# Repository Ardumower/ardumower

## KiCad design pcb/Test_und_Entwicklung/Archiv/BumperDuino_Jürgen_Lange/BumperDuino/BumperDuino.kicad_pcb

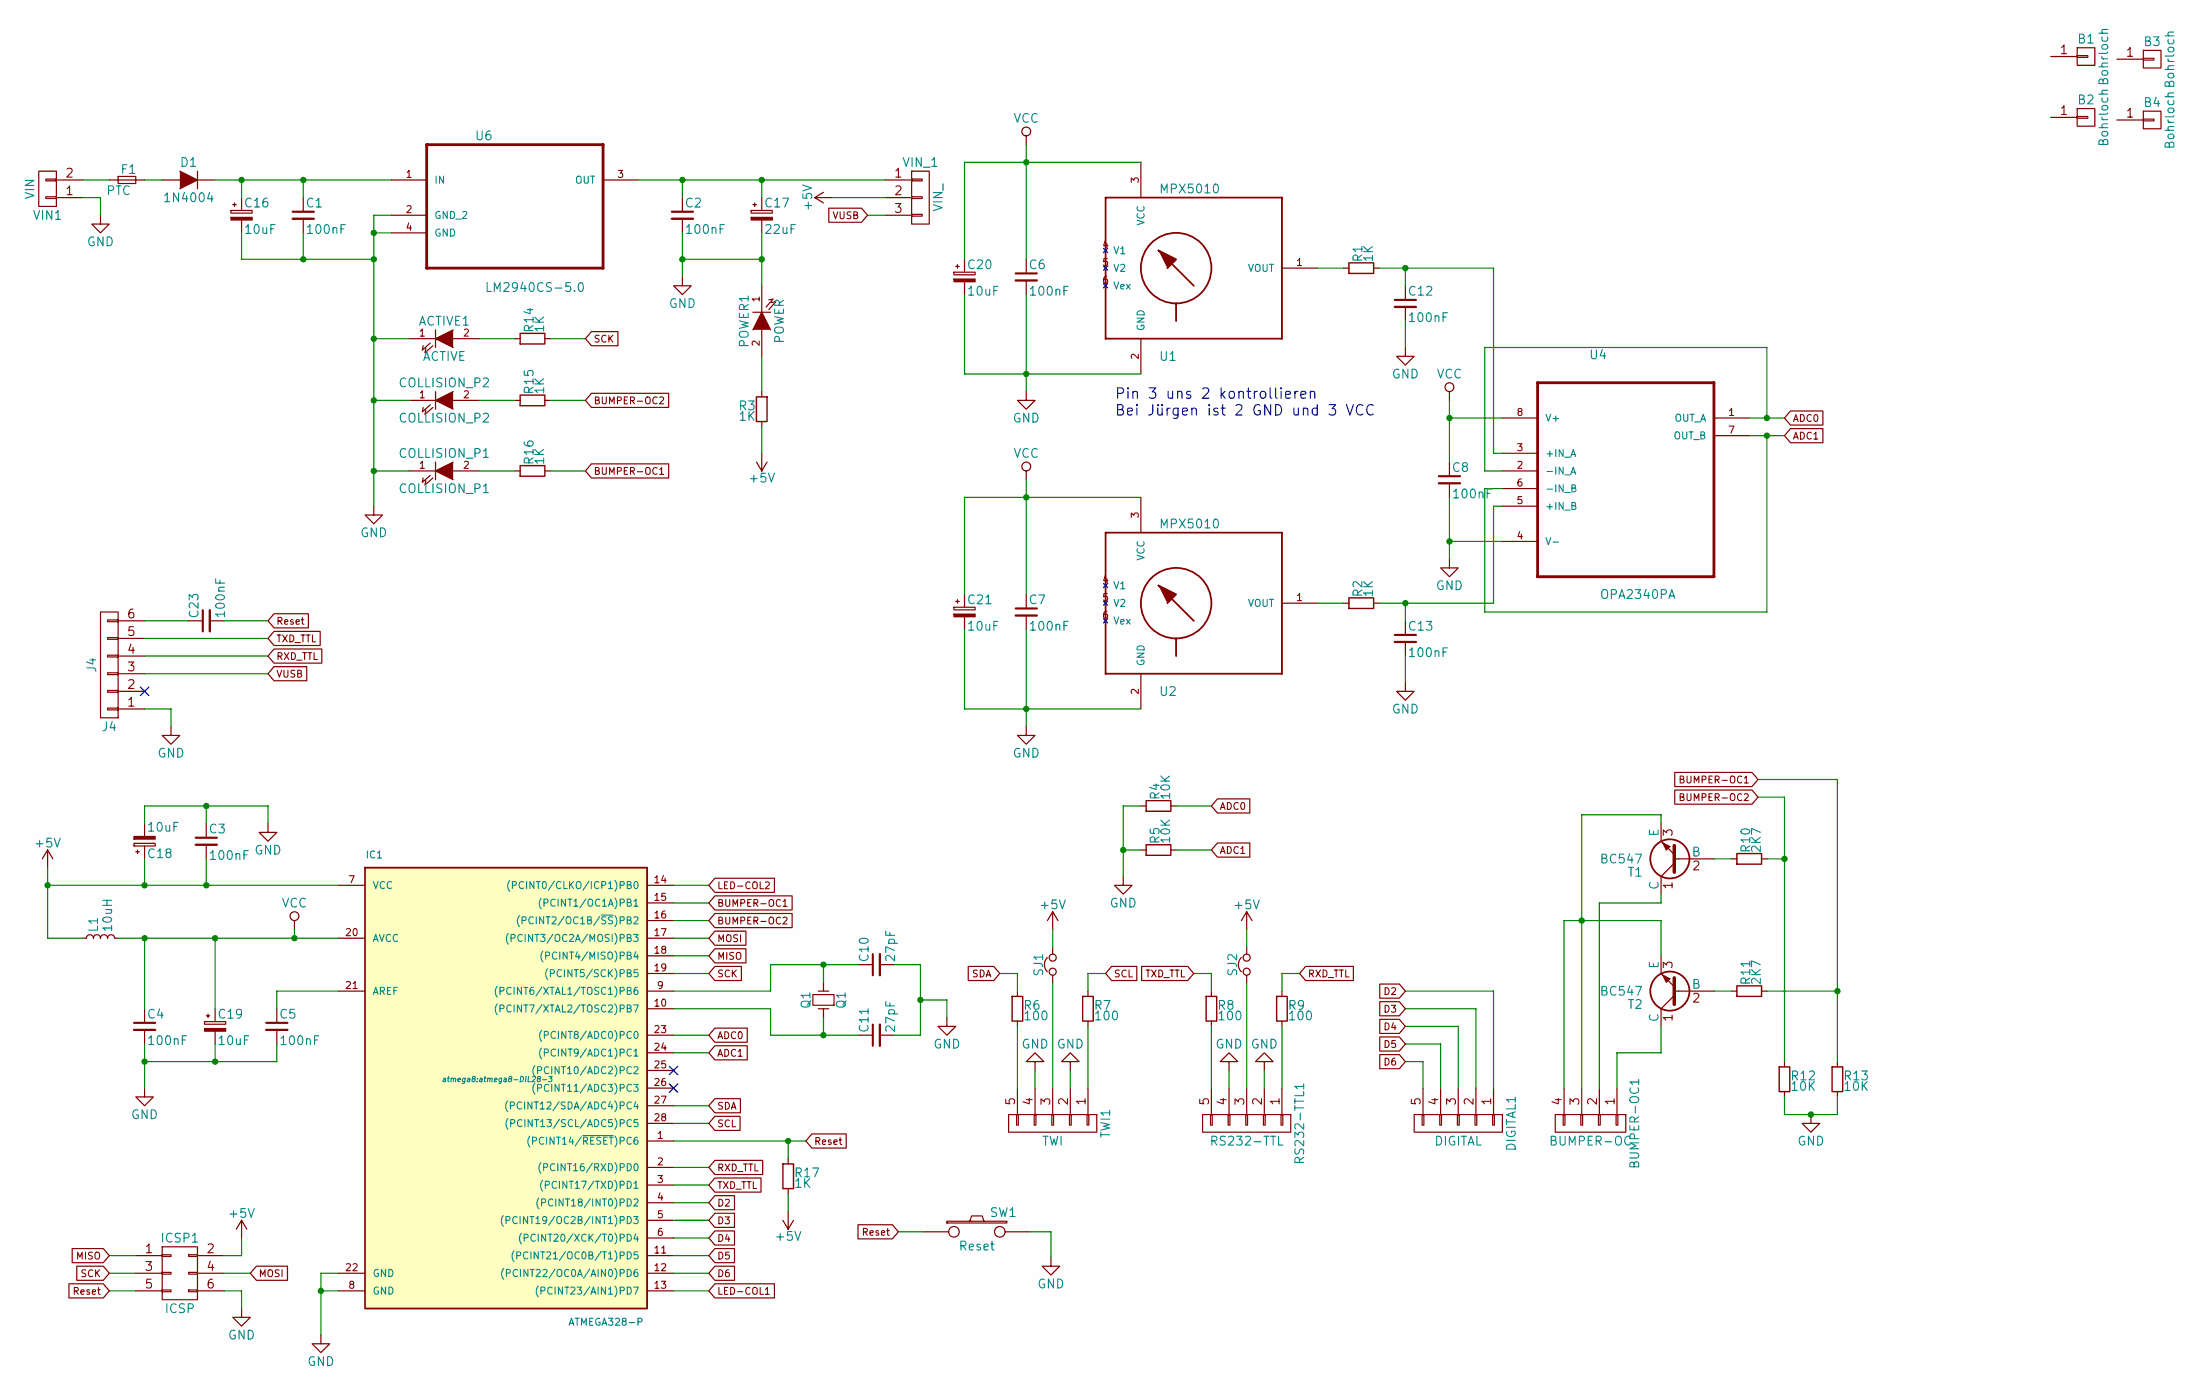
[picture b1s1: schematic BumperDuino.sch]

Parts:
ACTIVE1: ACTIVE; LED-3MM
B1, B2, B3, B4: Bohrloch; Bohrloch_3,2mm
BUMPER-OC1: BUMPER-OC; Pin_Header_Straight_1x04
C1, C2, C3, C4, C5, C6, C7, C8, C23: 100nF; C_Rect_L4_W2.5_P2.5
C10, C11: 27pF; C_Rect_L4_W2.5_P2.5
C12, C13: 100nF; C_Rect_L4_W2.5_P2.5_P5
C16, C18, C19, C20, C21: 10uF; Elko_vert_11x5mm_RM2.5
C17: 22uF; Elko_vert_11x5mm_RM2.5
COLLISION_P1: COLLISION_P1; LED-3MM
COLLISION_P2: COLLISION_P2; LED-3MM
D1: 1N4004; Diode_DO-35_SOD27_Horizontal_RM10
DIGITAL1: DIGITAL; Pin_Header_Straight_1x05
F1: PTC; Fuse_SMD1206_Reflow
IC1: ATMEGA328-P; atmega8-DIL28-3
ICSP1: ICSP; Pin_Header_Straight_2x03
J4: J4; Pin_Header_Straight_1x06
L1: 10uH; Resistor_Horizontal_RM10mm
POWER1: POWER; LED-3MM
Q1: Q1; Crystal_HC49-U_Vertical
R1, R2, R3, R14, R15, R16, R17: 1K; R_1206
R4, R5, R12, R13: 10K; R_1206
R6, R7, R8, R9: 100; R_1206
R10, R11: 2K7; R_1206
RS232-TTL1: RS232-TTL; Pin_Header_Straight_1x05
SJ1, SJ2: Jumper_NC_Small; Pin_Header_Straight_1x02
SW1: Reset; SW_SPST_FSMSM
T1, T2: BC547; TO-92_Molded_Narrow
TWI1: TWI; Pin_Header_Straight_1x05
U1, U2: MPX5010; 867C-H
U4: OPA2340PA; DIP254P762X508-8
U6: LM2940CS-5.0; TO254P1435X464-4N
VIN1: VIN; Pin_Header_Straight_1x02
VIN_1: VIN_; Pin_Header_Straight_1x03

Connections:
+5V: C3.2, C18.1, IC1.7 (VCC), ICSP1.2, L1.1, R3.2, R17.2, SJ1.2, SJ2.2, VIN_1.2
ADC0: IC1.23 ((PCINT8/ADC0)PC0), R4.2, U4.1 (OUT_A), U4.2 (-IN_A)
ADC1: IC1.24 ((PCINT9/ADC1)PC1), R5.2, U4.6 (-IN_B), U4.7 (OUT_B)
BUMPER-OC1: IC1.15 ((PCINT1/OC1A)PB1), R11.2, R13.1, R16.2
BUMPER-OC2: IC1.16 ((PCINT2/OC1B/~SS~)PB2), R10.2, R12.1, R15.2
D2: DIGITAL1.1, IC1.4 ((PCINT18/INT0)PD2)
D3: DIGITAL1.2, IC1.5 ((PCINT19/OC2B/INT1)PD3)
D4: DIGITAL1.3, IC1.6 ((PCINT20/XCK/T0)PD4)
D5: DIGITAL1.4, IC1.11 ((PCINT21/OC0B/T1)PD5)
D6: DIGITAL1.5, IC1.12 ((PCINT22/OC0A/AIN0)PD6)
GND: ACTIVE1.1 (K), C1.2, C2.2, C3.1, C4.2, C5.2, C6.2, C7.2, C8.2, C10.2, C11.2, C12.2, C13.2, C16.2, C17.2, C18.2, C19.2, C20.2, C21.2, COLLISION_P1.1 (K), COLLISION_P2.1 (K), IC1.8 (GND), IC1.22 (GND), ICSP1.6, J4.1, POWER1.1 (K), R4.1, R5.1, R12.2, R13.2, RS232-TTL1.2, RS232-TTL1.4, SW1.2, TWI1.2, TWI1.4, U1.2 (GND), U2.2 (GND), U4.4 (V-), U6.2 (GND_2), U6.4 (GND), VIN1.1
MISO: IC1.18 ((PCINT4/MISO)PB4), ICSP1.1
MOSI: IC1.17 ((PCINT3/OC2A/MOSI)PB3), ICSP1.4
unnamed: ACTIVE1.2 (A), R14.1
unnamed: BUMPER-OC1.1, T2.1 (C)
unnamed: BUMPER-OC1.2, T1.1 (C)
unnamed: BUMPER-OC1.3, BUMPER-OC1.4, T1.3 (E), T2.3 (E)
unnamed: C1.1, C16.1, D1.1 (K), U6.1 (IN)
unnamed: C5.1, IC1.21 (AREF)
unnamed: C10.1, IC1.9 ((PCINT6/XTAL1/TOSC1)PB6), Q1.2
unnamed: C11.1, IC1.10 ((PCINT7/XTAL2/TOSC2)PB7), Q1.1
unnamed: C12.1, R1.2, U4.3 (+IN_A)
unnamed: C13.1, R2.2, U4.5 (+IN_B)
unnamed: C2.1, C17.1, U6.3 (OUT), VIN_1.1
unnamed: C23.1, J4.6
unnamed: COLLISION_P1.2 (A), R16.1
unnamed: COLLISION_P2.2 (A), R15.1
unnamed: D1.2 (A), F1.2
unnamed: F1.1, VIN1.2
unnamed: POWER1.2 (A), R3.1
unnamed: R1.1, U1.1 (VOUT)
unnamed: R2.1, U2.1 (VOUT)
unnamed: R6.2, TWI1.5
unnamed: R7.2, TWI1.1
unnamed: R8.2, RS232-TTL1.5
unnamed: R9.2, RS232-TTL1.1
unnamed: R10.1, T1.2 (B)
unnamed: R11.1, T2.2 (B)
unnamed: RS232-TTL1.3, SJ2.1
unnamed: SJ1.1, TWI1.3
RXD_TTL: IC1.2 ((PCINT16/RXD)PD0), J4.4, R9.1
Reset: C23.2, IC1.1 ((PCINT14/~RESET~)PC6), ICSP1.5, R17.1, SW1.1
SCK: IC1.19 ((PCINT5/SCK)PB5), ICSP1.3, R14.2
SCL: IC1.28 ((PCINT13/SCL/ADC5)PC5), R7.1
SDA: IC1.27 ((PCINT12/SDA/ADC4)PC4), R6.1
TXD_TTL: IC1.3 ((PCINT17/TXD)PD1), J4.5, R8.1
VCC: C4.1, C6.1, C7.1, C8.1, C19.1, C20.1, C21.1, IC1.20 (AVCC), L1.2, U1.3 (VCC), U2.3 (VCC), U4.8 (V+)
VUSB: J4.3, VIN_1.3

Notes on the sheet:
Pin 3 uns 2 kontrollieren Bei Jürgen ist 2 GND und 3 VCC

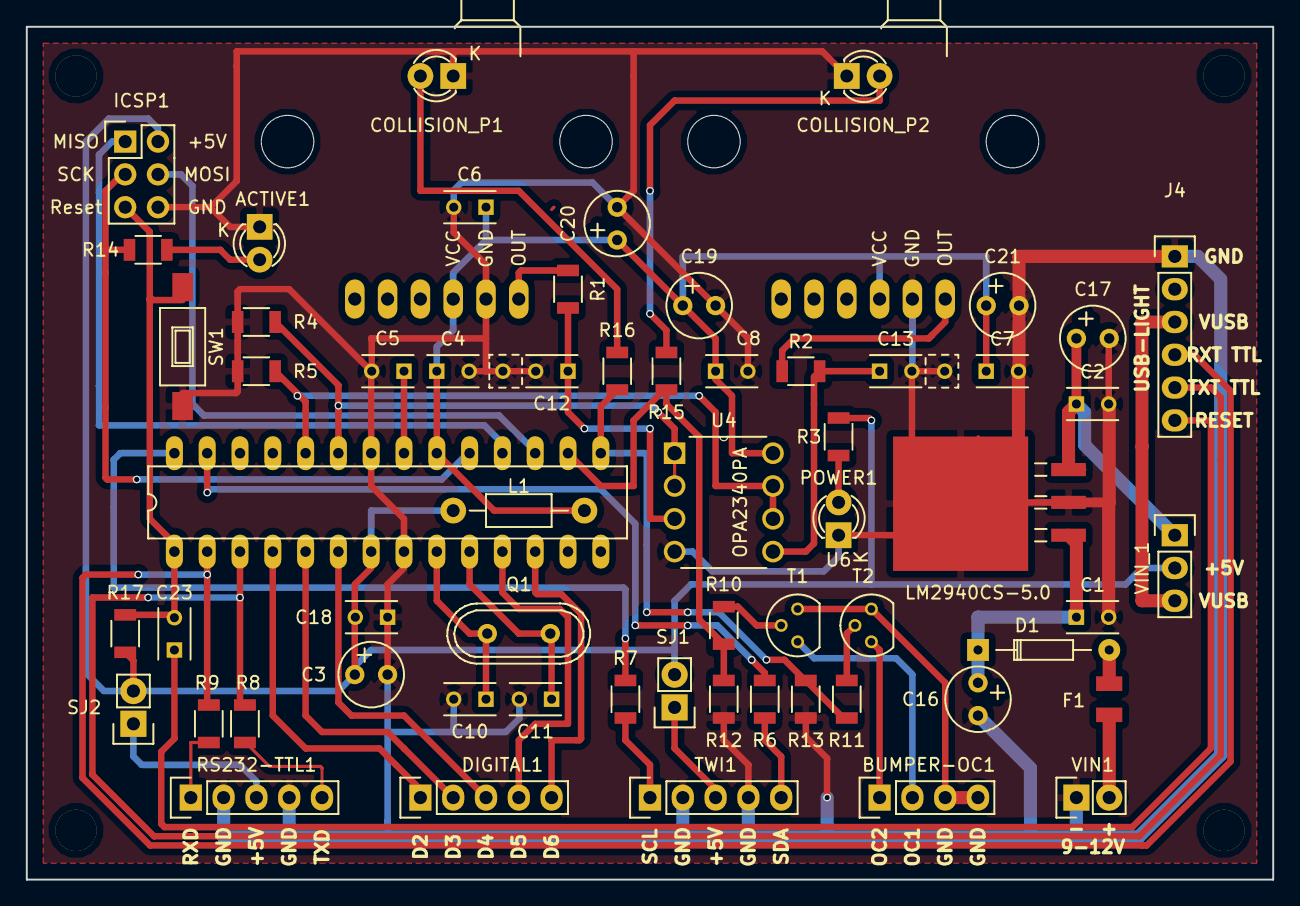
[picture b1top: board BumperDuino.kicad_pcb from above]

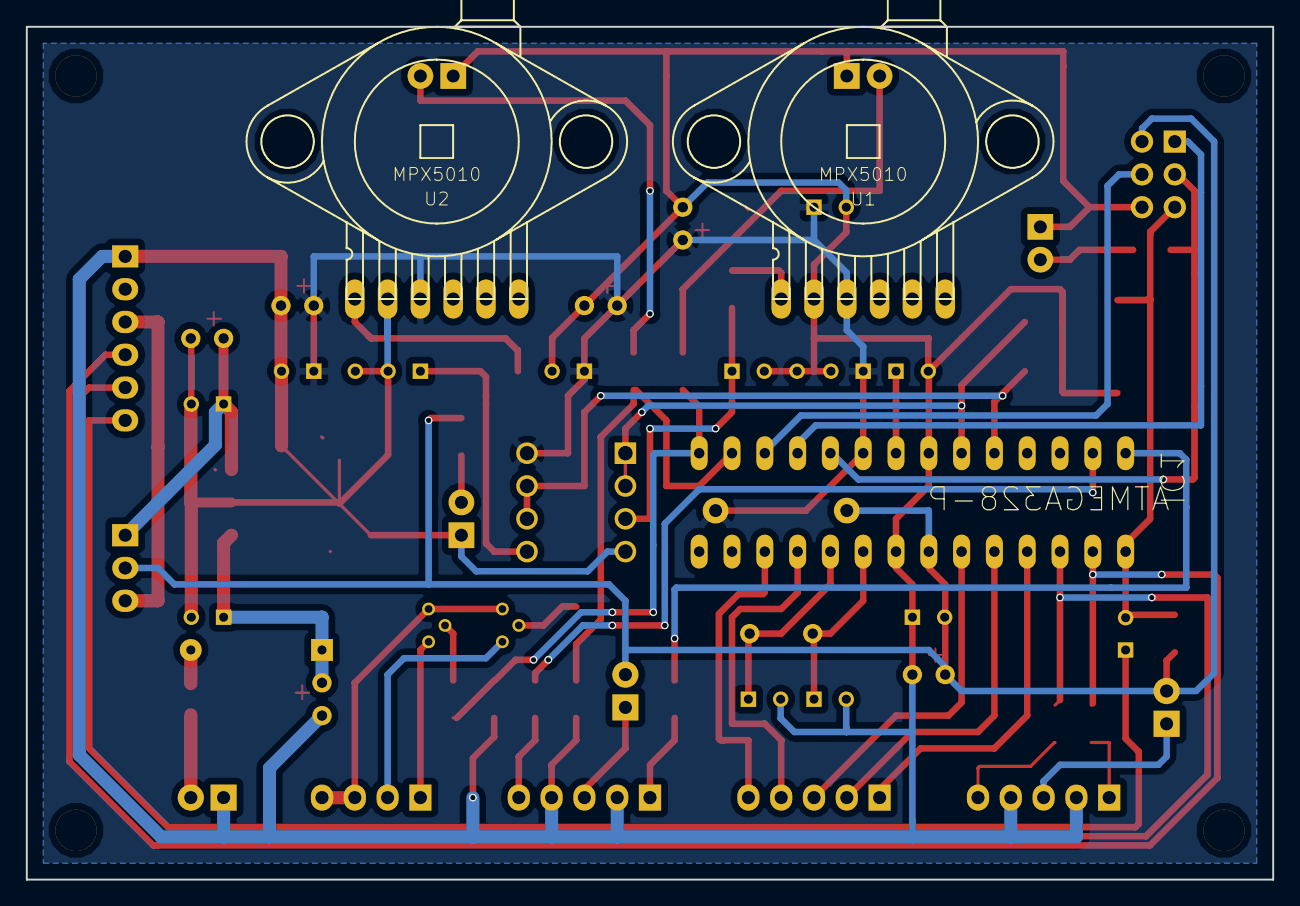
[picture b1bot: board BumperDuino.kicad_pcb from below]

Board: 2 copper layers, 96.5 x 66.0 mm, 66 parts (2 on the bottom side), 48 nets.

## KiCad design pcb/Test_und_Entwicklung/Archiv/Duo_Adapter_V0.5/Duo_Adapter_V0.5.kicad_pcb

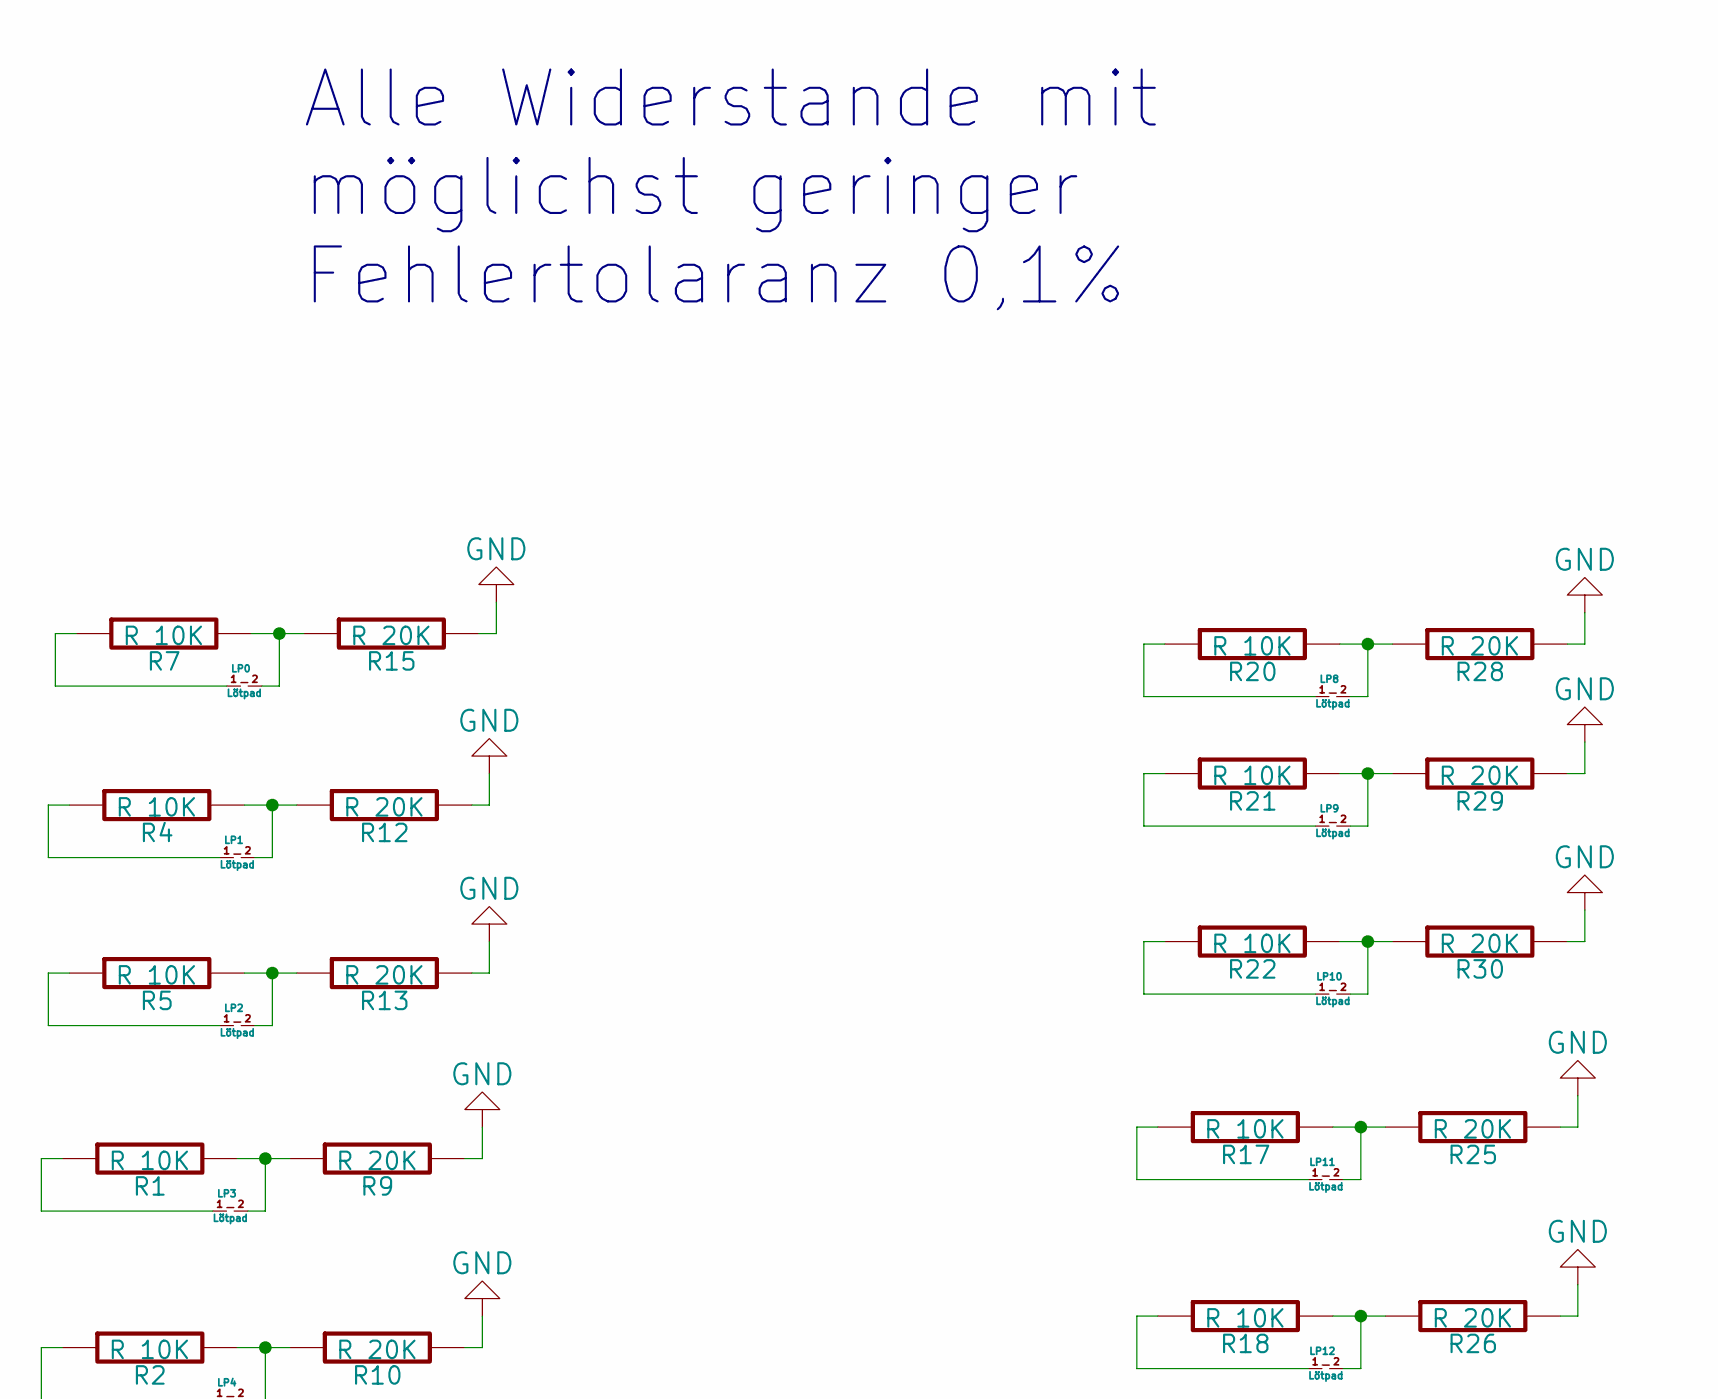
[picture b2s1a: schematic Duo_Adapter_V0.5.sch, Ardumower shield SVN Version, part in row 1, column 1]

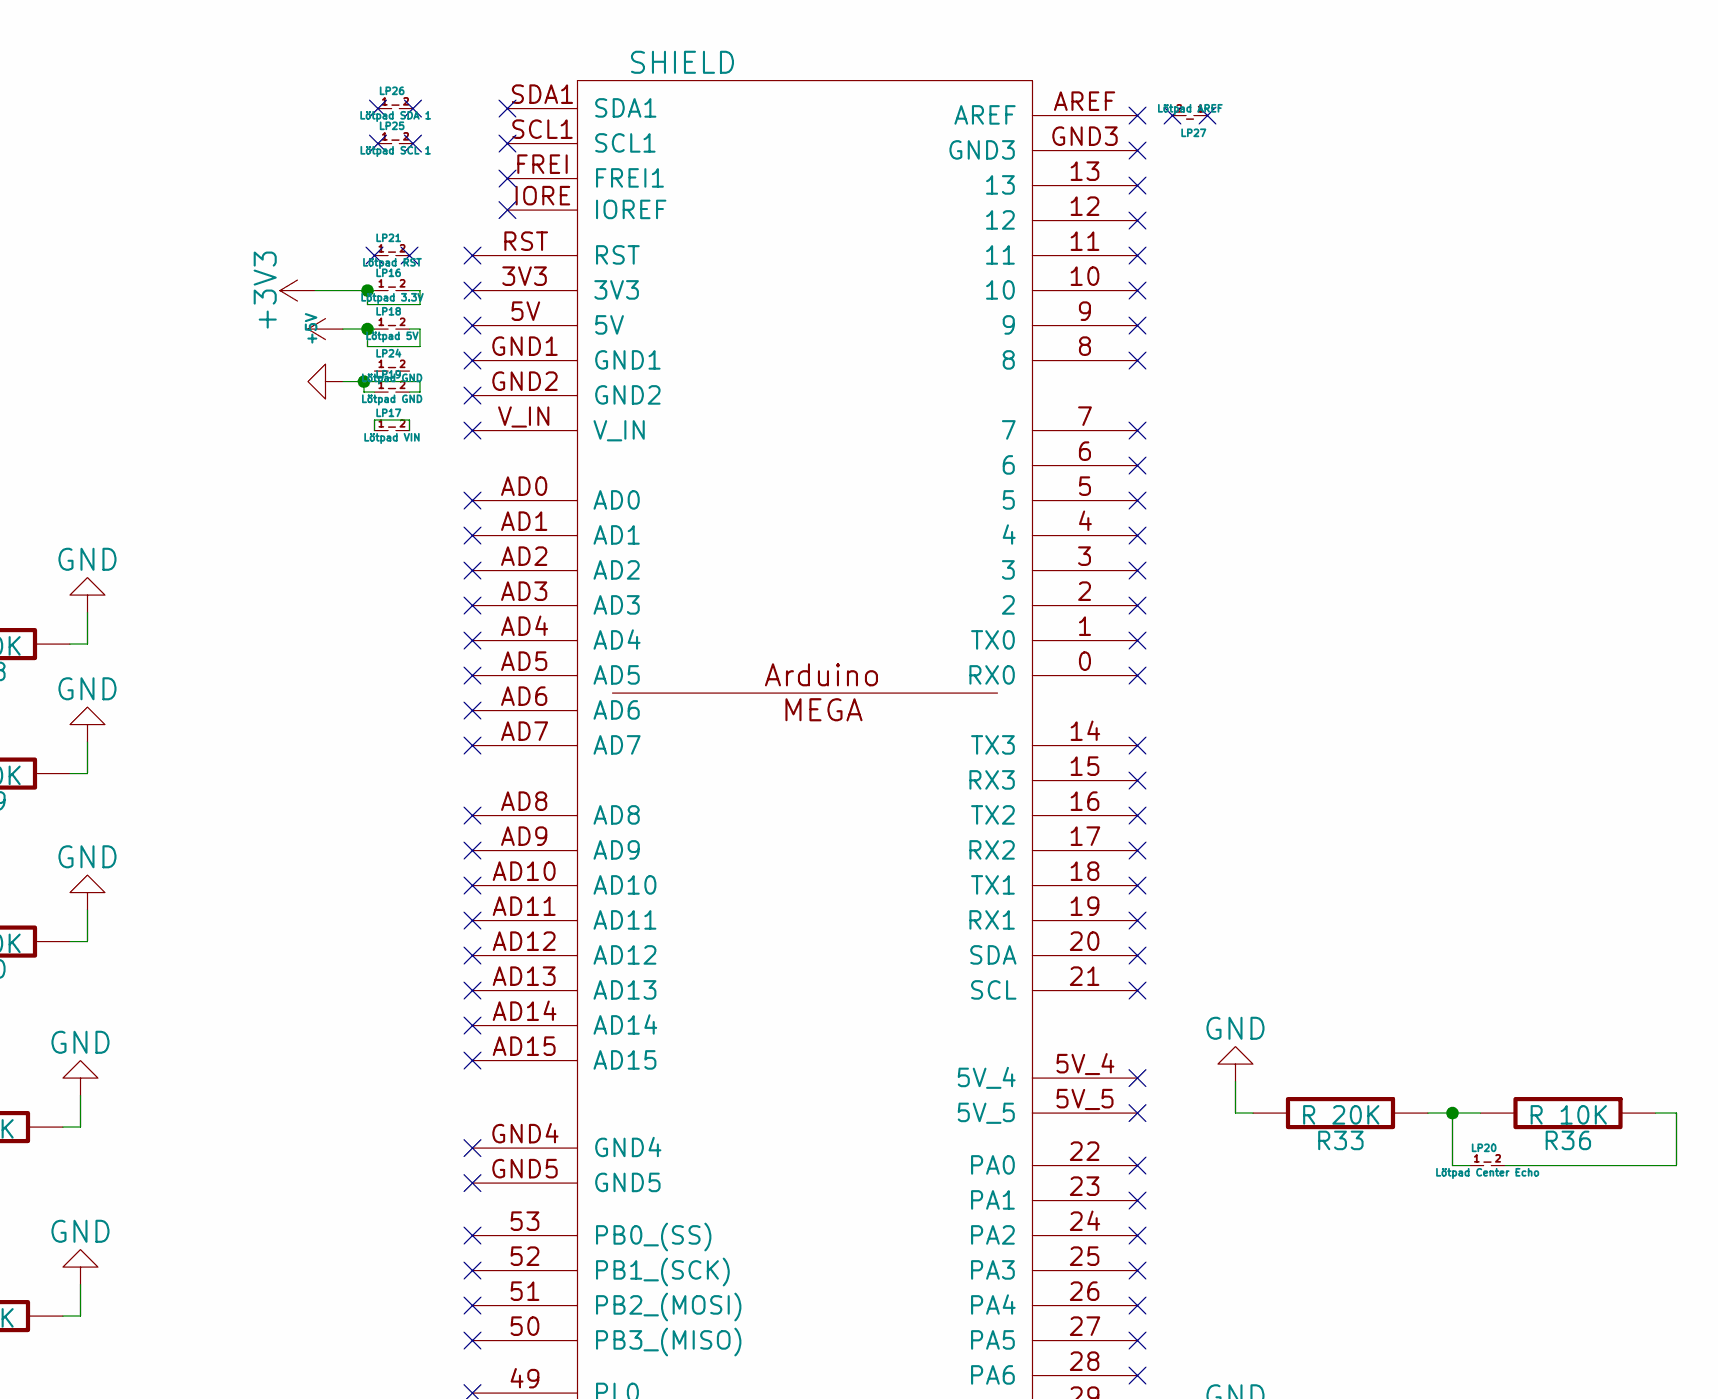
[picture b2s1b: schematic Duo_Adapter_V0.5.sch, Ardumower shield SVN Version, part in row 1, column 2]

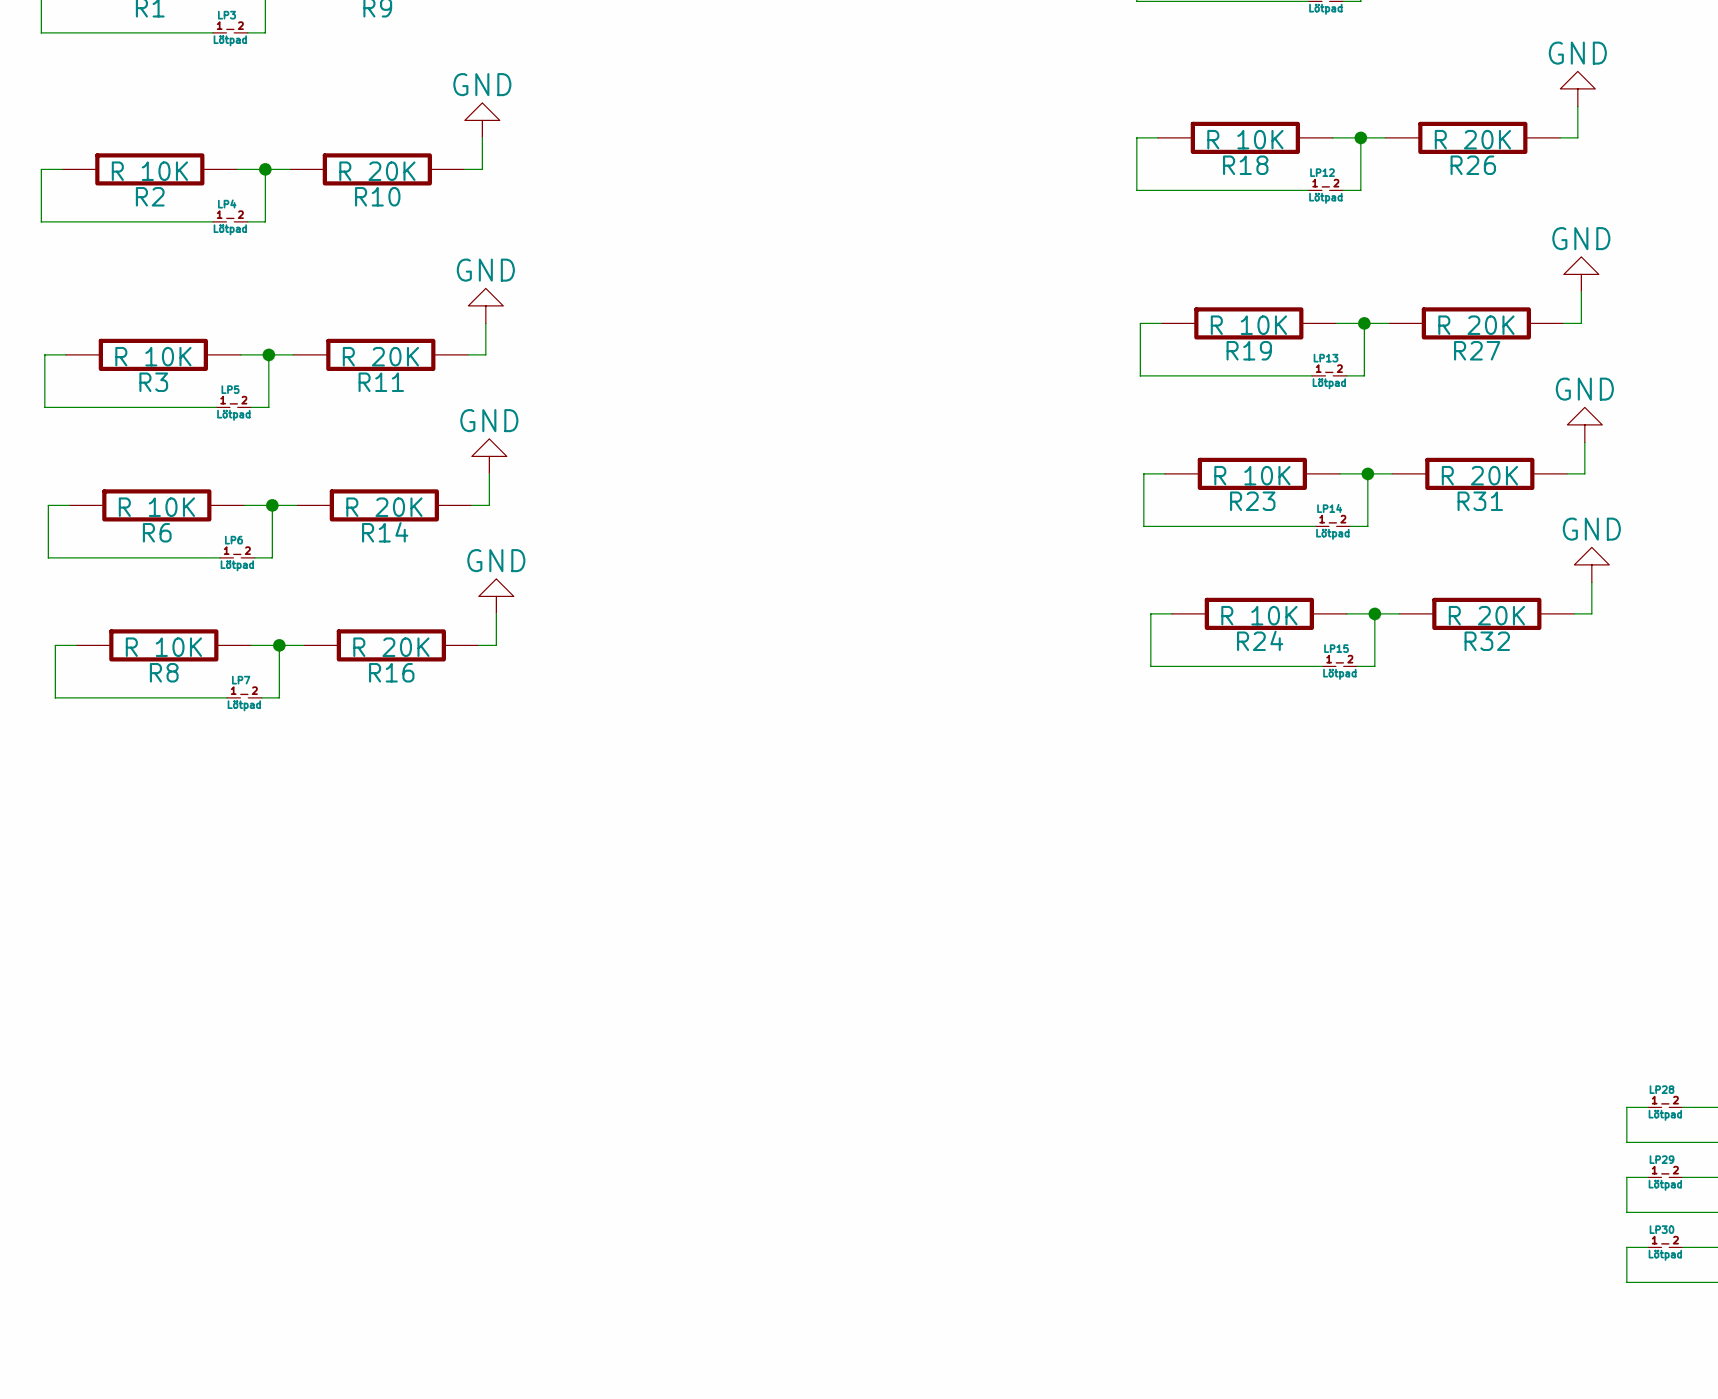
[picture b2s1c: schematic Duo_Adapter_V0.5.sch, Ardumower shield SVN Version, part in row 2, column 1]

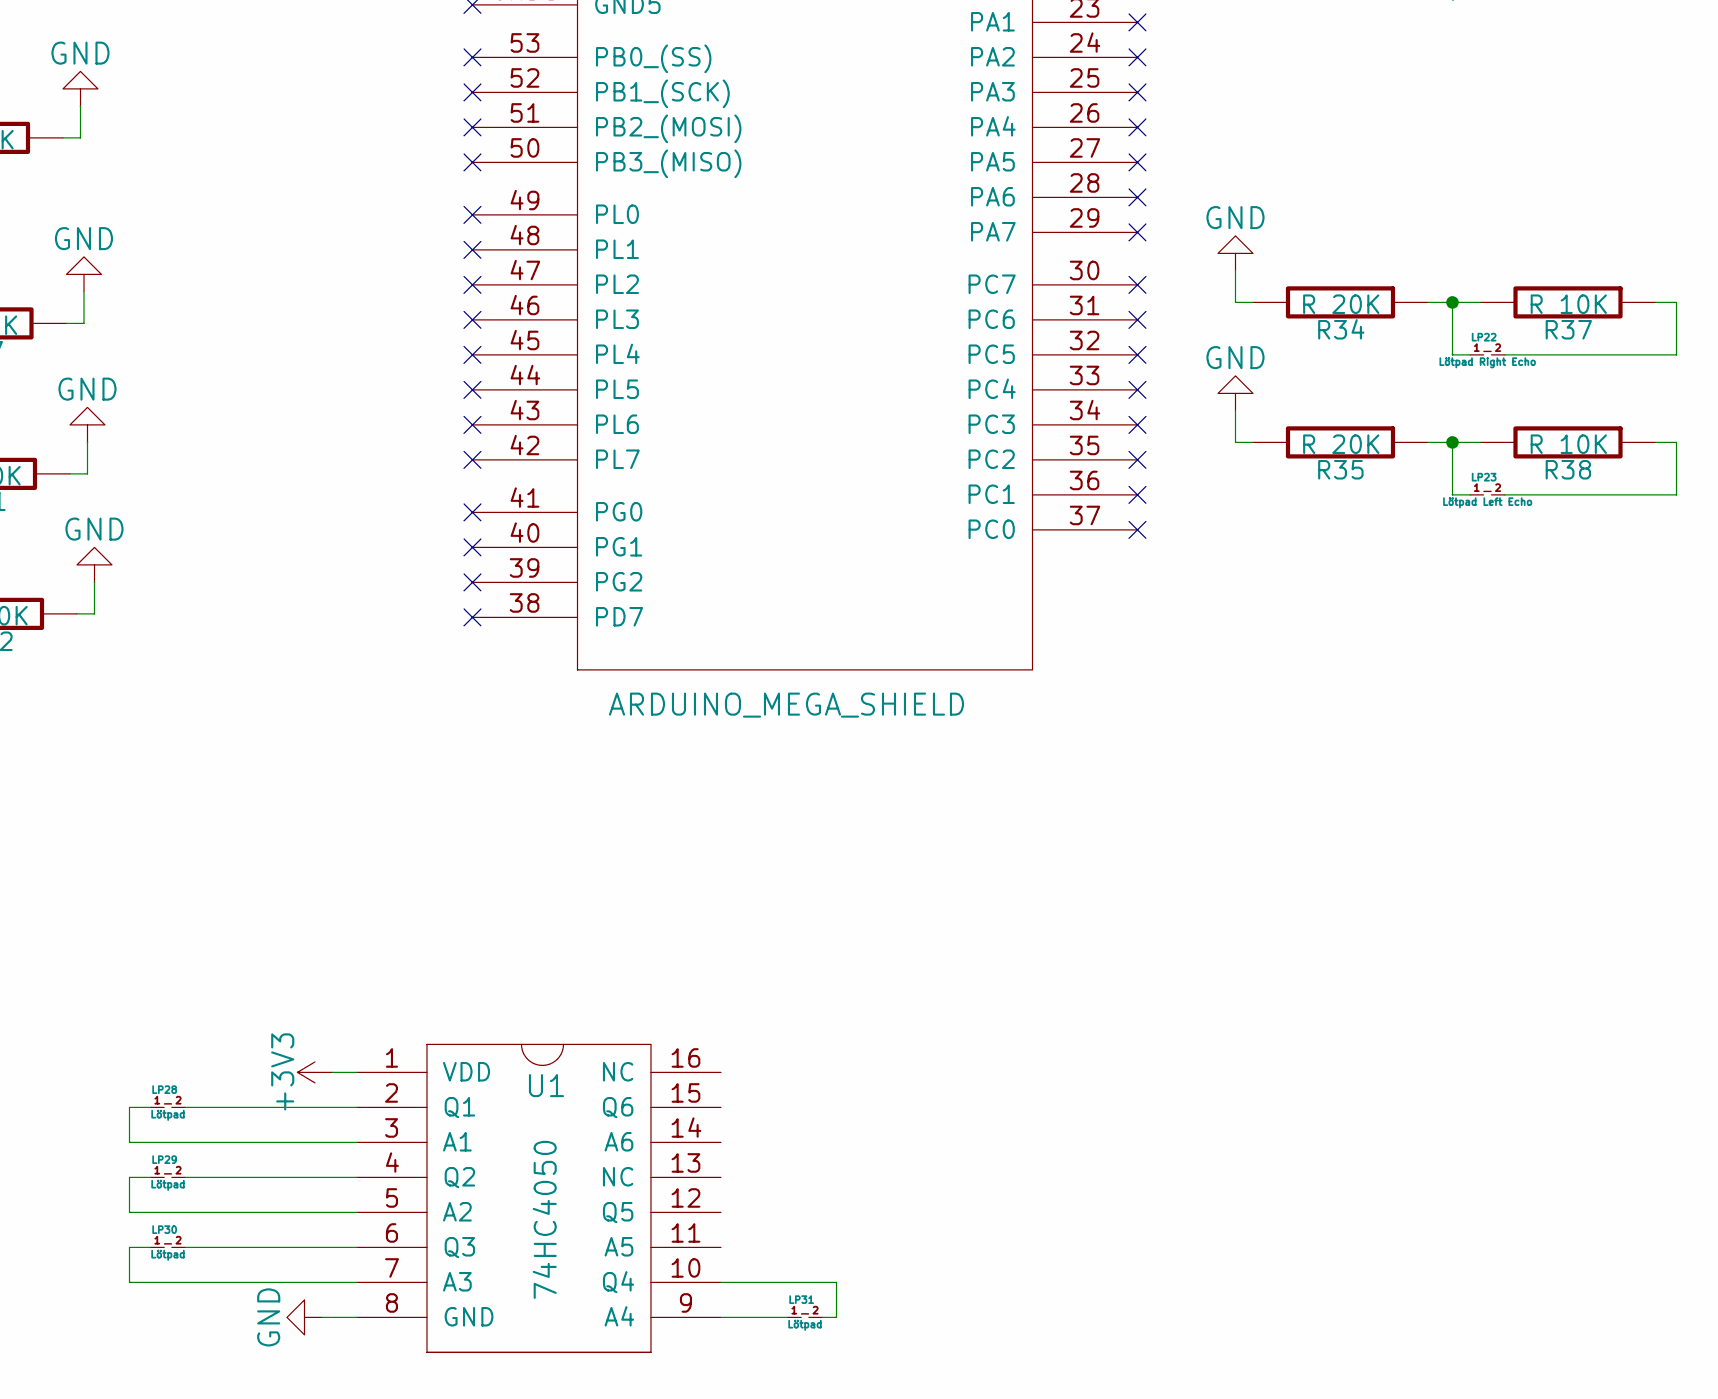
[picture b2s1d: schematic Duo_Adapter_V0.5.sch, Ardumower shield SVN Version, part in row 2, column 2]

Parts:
LP0, LP1, LP2, LP3, LP4, LP5, LP6, LP7, LP8, LP9, LP10, LP11, LP12, LP13, LP14, LP15, LP28, LP29, LP30, LP31: Lötpad; Lötpad_1x02_Buchse
LP16: Lötpad 3.3V; Lötpad_1x02_Buchse
LP17: Lötpad VIN; Lötpad_1x02_Buchse
LP18: Lötpad 5V; Lötpad_1x02_Buchse
LP19, LP24: Lötpad GND; Lötpad_1x02_Buchse
LP20: Lötpad Center Echo; Lötpad_1x02_Buchse
LP21: Lötpad RST; Lötpad_1x02_Buchse
LP22: Lötpad Right Echo; Lötpad_1x02_Buchse
LP23: Lötpad Left Echo; Lötpad_1x02_Buchse
LP25: Lötpad SCL 1; Lötpad_1x02_Buchse
LP26: Lötpad SDA 1; Lötpad_1x02_Buchse
LP27: Lötpad AREF; Lötpad_1x02_Buchse
R1, R2, R3, R4, R5, R6, R7, R8, R17, R18, R19, R20, R21, R22, R23, R24, R36, R37, R38: R 10K; Resistor_Horizontal_RM10mm
R9, R10, R11, R12, R13, R14, R15, R16, R25, R26, R27, R28, R29, R30, R31, R32, R33, R34, R35: R 20K; Resistor_Horizontal_RM10mm
SHIELD1: ARDUINO_MEGA_SHIELD; ARDUINO_MEGA_SHIELD_DUO_3D
U1: 74HC4050; DIP-16__300

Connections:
+3V3: LP16.1, LP16.2, U1.1 (VDD)
+5V: LP18.1, LP18.2
GND: LP19.1, LP19.2, R9.2, R10.2, R11.2, R12.2, R13.2, R14.2, R15.2, R16.2, R25.2, R26.2, R27.2, R28.2, R29.2, R30.2, R31.2, R32.2, R33.2, R34.2, R35.2, U1.8 (GND)
unnamed: LP0.1, R7.1
unnamed: LP0.2, R7.2, R15.1
unnamed: LP1.1, R4.1
unnamed: LP1.2, R4.2, R12.1
unnamed: LP2.1, R5.1
unnamed: LP2.2, R5.2, R13.1
unnamed: LP3.1, R1.1
unnamed: LP3.2, R1.2, R9.1
unnamed: LP4.1, R2.1
unnamed: LP4.2, R2.2, R10.1
unnamed: LP5.1, R3.1
unnamed: LP5.2, R3.2, R11.1
unnamed: LP6.1, R6.1
unnamed: LP6.2, R6.2, R14.1
unnamed: LP7.1, R8.1
unnamed: LP7.2, R8.2, R16.1
unnamed: LP8.1, R20.1
unnamed: LP8.2, R20.2, R28.1
unnamed: LP9.1, R21.1
unnamed: LP9.2, R21.2, R29.1
unnamed: LP10.1, R22.1
unnamed: LP10.2, R22.2, R30.1
unnamed: LP11.1, R17.1
unnamed: LP11.2, R17.2, R25.1
unnamed: LP12.1, R18.1
unnamed: LP12.2, R18.2, R26.1
unnamed: LP13.1, R19.1
unnamed: LP13.2, R19.2, R27.1
unnamed: LP14.1, R23.1
unnamed: LP14.2, R23.2, R31.1
unnamed: LP15.1, R24.1
unnamed: LP15.2, R24.2, R32.1
unnamed: LP17.1, LP17.2
unnamed: LP20.1, R33.1, R36.2
unnamed: LP20.2, R36.1
unnamed: LP22.1, R34.1, R37.2
unnamed: LP22.2, R37.1
unnamed: LP23.1, R35.1, R38.2
unnamed: LP23.2, R38.1
unnamed: LP28.1, U1.3 (A1)
unnamed: LP28.2, U1.2 (Q1)
unnamed: LP29.1, U1.5 (A2)
unnamed: LP29.2, U1.4 (Q2)
unnamed: LP30.1, U1.7 (A3)
unnamed: LP30.2, U1.6 (Q3)
unnamed: LP31.1, U1.9 (A4)
unnamed: LP31.2, U1.10 (Q4)

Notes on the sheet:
Alle Widerstande mit möglichst geringer Fehlertolaranz 0,1%

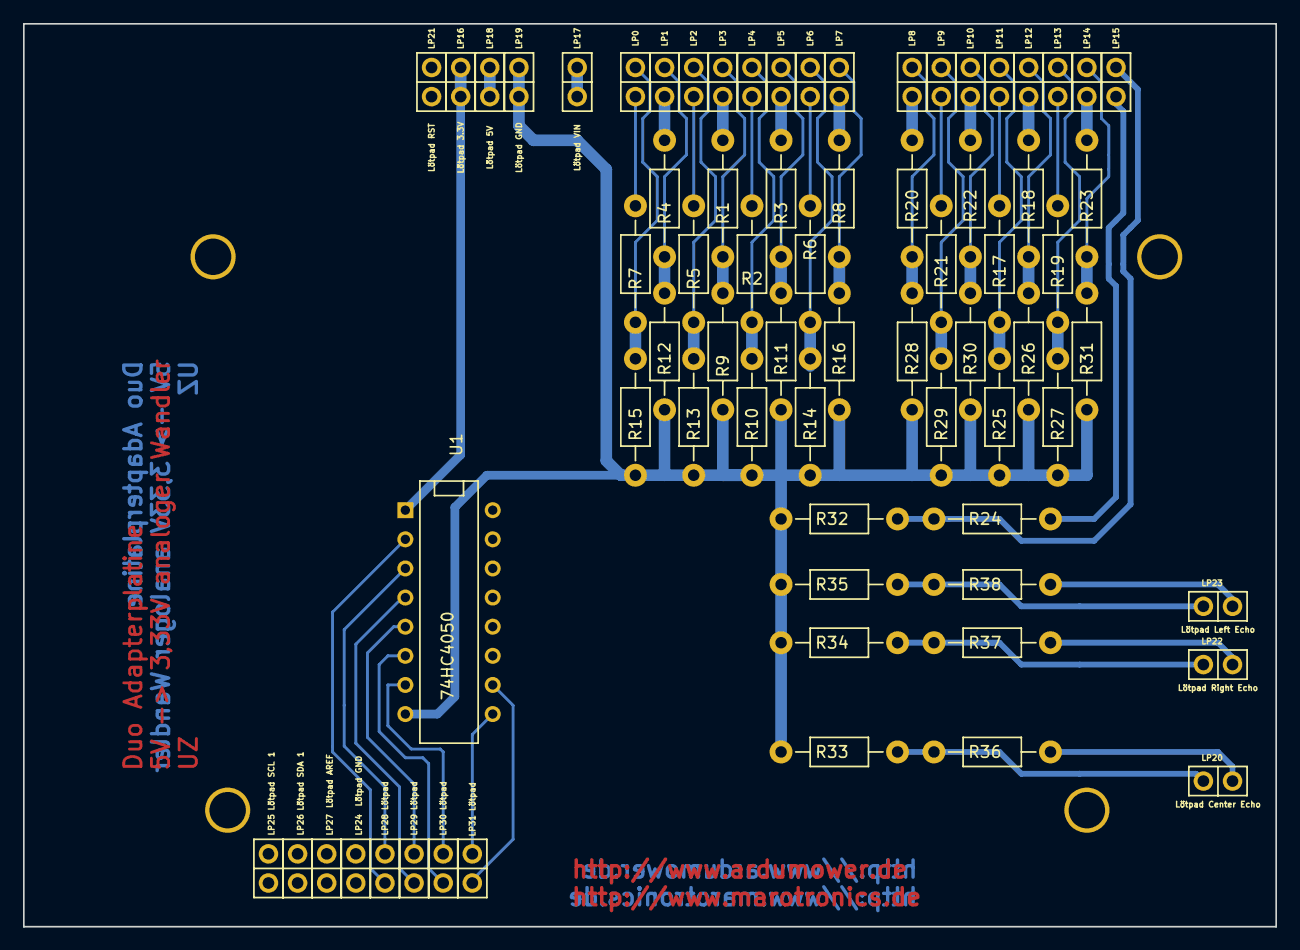
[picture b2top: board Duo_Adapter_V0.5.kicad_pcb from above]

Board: 2 copper layers, 109.2 x 78.7 mm, 72 parts (1 on the bottom side), 50 nets.

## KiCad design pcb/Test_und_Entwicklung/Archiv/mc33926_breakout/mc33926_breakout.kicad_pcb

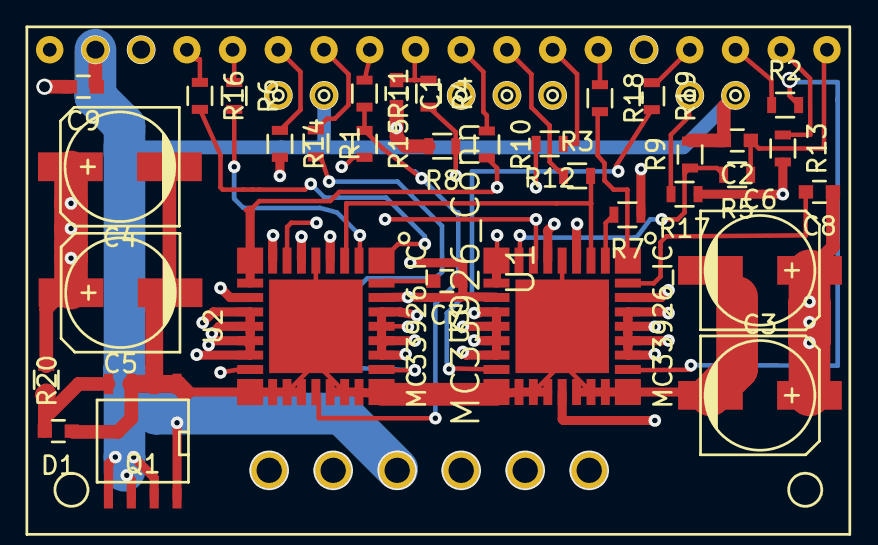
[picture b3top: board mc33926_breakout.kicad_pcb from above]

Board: 4 copper layers, 34 parts (0 on the bottom side), 41 nets.

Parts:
C1, C2: 0.47uF; C_0603
C3, C4, C5, C6: 47uF; c_elec_6.3x5.8
C7, C8: 33nF; C_0603
C9: 0.1uF; C_0603
D1: ZENER; C_0603
Q1: MOSN-SO8; SOIC-8-N
R1, R2, R3, R4, R5, R6, R7, R10, R11, R12, R13, R14, R16, R18, R19: 1k; R_0603
R8, R9: 220; R_0603
R15, R17: 10k; R_0603
R20: 100k; R_0603
U1: MC33926_Conn; mc33926_breakout_footprint
U2, U3: MC33926_IC; mc33926_ic_pqfn32

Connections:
ENP: R10.2, U2.9, U2.10, U3.9, U3.10
FGND: C3.2, C4.2, C5.2, C6.2, D1.1, Q1.1, Q1.2, Q1.3, U2.5, U2.17, U2.18, U2.19, U2.20, U2.22, U2.23, U2.24, U2.25, U2.33, U3.5, U3.17, U3.18, U3.19, U3.20, U3.22, U3.23, U3.24, U3.25, U3.33
GND: C1.2, C2.2, C9.1, Q1.5, Q1.6, Q1.7, Q1.8, R8.2, R9.2, U1.2, U1.21
INVP: R12.2, U2.7, U3.7
M1OUT1: U1.19, U2.12, U2.13, U2.14, U2.15
M1OUT2: U1.20, U2.27, U2.28, U2.29, U2.30
M2OUT1: U1.23, U3.12, U3.13, U3.14, U3.15
M2OUT2: U1.24, U3.27, U3.28, U3.29, U3.30
unnamed: C1.1, R4.1, U1.9
unnamed: C2.1, R5.1, U1.18
unnamed: C7.2, U2.32
unnamed: C8.2, U3.32
unnamed: D1.2, Q1.4, R20.1
unnamed: R1.1, U1.7
unnamed: R1.2, U2.26
unnamed: R2.1, U1.16
unnamed: R2.2, U3.26
unnamed: R3.1, U1.11
unnamed: R4.2, R8.1, U2.8
unnamed: R5.2, R9.1, U3.8
unnamed: R6.1, U1.5
unnamed: R6.2, U2.2
unnamed: R7.1, U1.14
unnamed: R7.2, U3.2
unnamed: R10.1, U1.10
unnamed: R11.1, U1.8
unnamed: R11.2, R15.1, U2.21
unnamed: R12.1, U1.12
unnamed: R13.1, U1.17
unnamed: R13.2, R17.1, U3.21
unnamed: R14.1, U1.6
unnamed: R14.2, U2.16
unnamed: R16.1, U1.4
unnamed: R16.2, U2.1
unnamed: R18.1, U1.13
unnamed: R18.2, U3.1
unnamed: R19.1, U1.15
unnamed: R19.2, U3.16
SLEWP: R3.2, U2.3, U3.3
VIN: C3.1, C4.1, C5.1, C6.1, C7.1, C8.1, C9.2, R20.2, U1.1, U1.22, U2.4, U2.6, U2.11, U2.31, U3.4, U3.6, U3.11, U3.31
Vdd: R15.2, R17.2, U1.3

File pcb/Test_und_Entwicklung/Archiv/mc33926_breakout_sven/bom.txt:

C1, C2  - 0.47uF 10V  0603  	Farnell MC0603X474K100CT   
C3,C4,C5,C6   - 47uF 35V   6.3x5.8  Mouser EEE-FK1V470AP  
C7,C8  - 33nF  50V 0603   Farnell MC0603B333K500CT  
C9  - 0.1uF 35V  0603    Farnell CGA2B3X7R1V104K050BB  
D1  - Zener 30V  0603    Mouser 652-CD0603-Z30
Q1  - MOSFET N-Channel 30V  SO8   Mouser 78-SI4010DY-T1-GE3    
R1,R2,R3,R4,R5,R6,R7,R10,R11,R12,R13,R14,R16,R18,R19 -  1k 5% 0603 
R8,R9  - 220 5%   0603
R15,R17 - 10k  5% 0603
R20 - 100k  5%  0603
U2,U3 - Freescale MC33926PNB  QFN-EP 32

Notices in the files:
pcb/Test_und_Entwicklung/Archiv/megashield_v1/ardumower mega shield V1.00.kicad_pcb:
(C) 2014 RFsolution
